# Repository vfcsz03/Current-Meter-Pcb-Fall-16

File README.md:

# Current-Meter-Pcb-Fall-16
Pcb-Design Fall 2016

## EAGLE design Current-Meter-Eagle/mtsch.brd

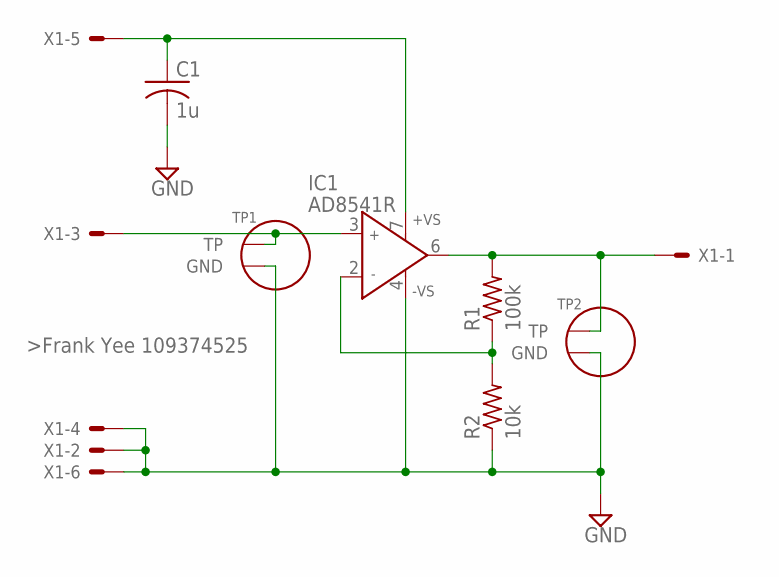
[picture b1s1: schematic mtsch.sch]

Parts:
C1: 1u; C3216
IC1: AD8541R; SO8
R1: 100k; M2012
R2: 10k; M2012
TP1, TP2: TESTPOINT; TPXPACK
X1: 22-23-2061

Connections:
GND: C1.2, IC1.4 (-VS), R2.1, TP1.GND, TP2.GND, X1.2, X1.4, X1.6
unnamed: C1.1, IC1.7 (+VS), X1.5
unnamed: IC1.3 (IN+), TP1.TP, X1.3
unnamed: IC1.6 (OUT), R1.2, TP2.TP, X1.1
unnamed: IC1.2 (IN-), R1.1, R2.2

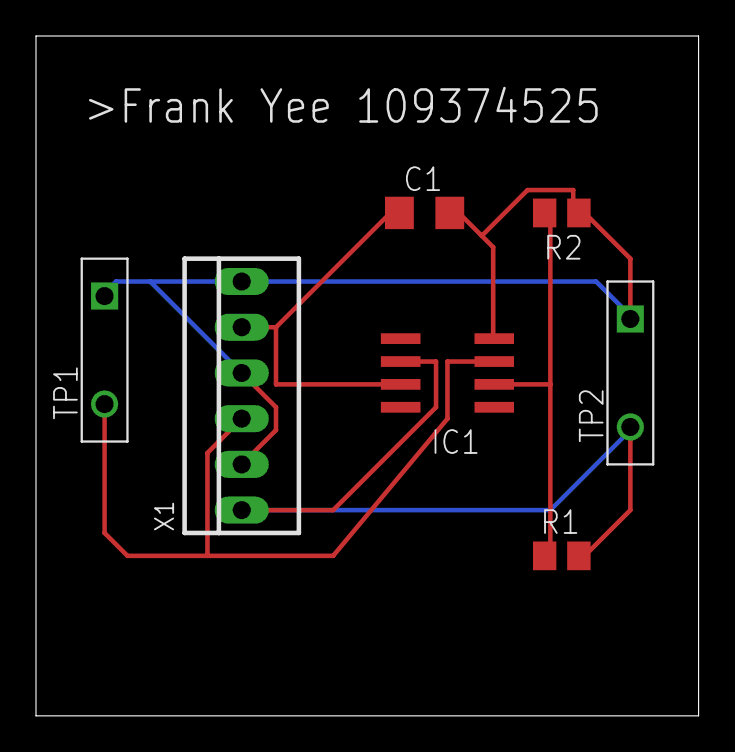
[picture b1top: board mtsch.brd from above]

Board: 2 copper layers, 36.8 x 37.8 mm, 7 parts (0 on the bottom side), 5 nets.

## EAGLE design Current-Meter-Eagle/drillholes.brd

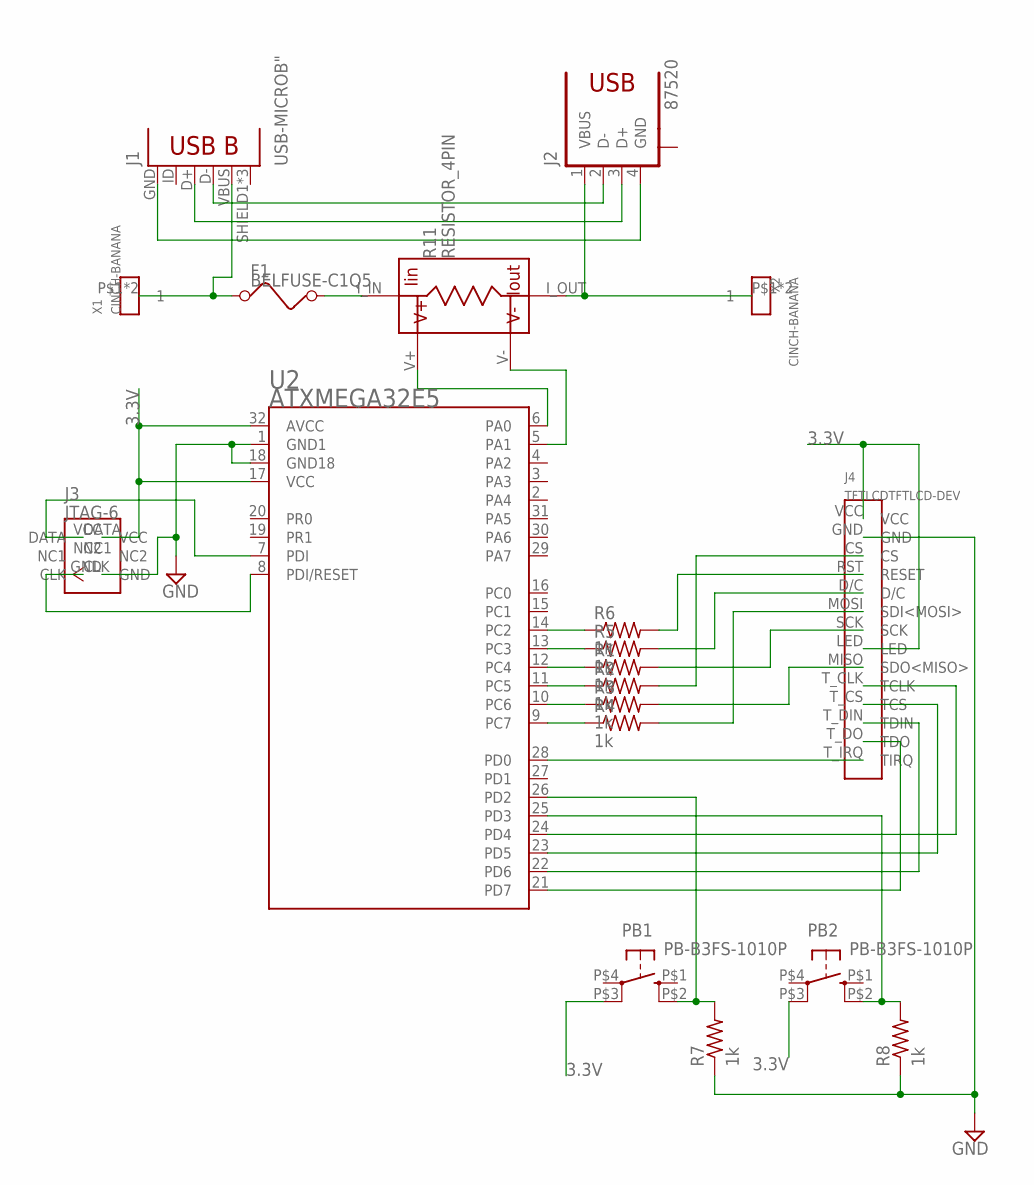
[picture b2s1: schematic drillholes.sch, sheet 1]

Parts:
ATXMEGA32E5: U2; TQFP32-08
F1: BELFUSE-C1Q5
J1: USB-MICROB"; USB-B-MICRO-SMD_V03
J2: 87520
J3: JTAG-6; JTAG6
J4: TFTLCDTFTLCD-DEV; TFTLCD
PB1, PB2: PB-B3FS-1010P
R1, R2, R3, R4, R5, R6, R7, R8: 1k; RC1206
R11: RESISTOR_4PIN
X1, X2: CINCH-BANANA

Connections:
3.3V: ATXMEGA32E5.17 (VCC), ATXMEGA32E5.32 (AVCC), J3.VCC, J4.LED, J4.VCC, PB1.P$3 (SW3), PB2.P$3 (SW3); also elsewhere on the board
GND: ATXMEGA32E5.1 (GND1), ATXMEGA32E5.18 (GND18), J3.GND, J4.GND, R7.P$1 (1), R8.P$1 (1); also elsewhere on the board
unnamed: ATXMEGA32E5.7 (PDI), J3.DATA
unnamed: ATXMEGA32E5.8 (PDI/RESET), J3.CLK
unnamed: ATXMEGA32E5.9 (PC7), R4.P$1 (1)
unnamed: ATXMEGA32E5.10 (PC6), R3.P$1 (1)
unnamed: ATXMEGA32E5.11 (PC5), R2.P$1 (1)
unnamed: ATXMEGA32E5.12 (PC4), R1.P$1 (1)
unnamed: J4.MOSI (SDI<MOSI>), R4.P$2 (2)
unnamed: J4.MISO (SDO<MISO>), R3.P$2 (2)
unnamed: J4.SCK, R1.P$2 (2)
unnamed: J4.CS, R2.P$2 (2)
unnamed: ATXMEGA32E5.14 (PC2), R6.P$1 (1)
unnamed: J4.RST (RESET), R6.P$2 (2)
unnamed: ATXMEGA32E5.13 (PC3), R5.P$1 (1)
unnamed: J4.D/C, R5.P$2 (2)
unnamed: ATXMEGA32E5.28 (PD0), J4.T_IRQ (TIRQ)
unnamed: ATXMEGA32E5.21 (PD7), J4.T_DO (TDO)
unnamed: ATXMEGA32E5.22 (PD6), J4.T_DIN (TDIN)
unnamed: ATXMEGA32E5.23 (PD5), J4.T_CS (TCS)
unnamed: ATXMEGA32E5.24 (PD4), J4.T_CLK (TCLK)
unnamed: ATXMEGA32E5.26 (PD2), PB1.P$2 (SW2), R7.P$2 (2)
unnamed: ATXMEGA32E5.25 (PD3), PB2.P$2 (SW2), R8.P$2 (2)
unnamed: ATXMEGA32E5.6 (PA0), R11.V+
unnamed: ATXMEGA32E5.5 (PA1), R11.V-
unnamed: F1.P$1 (1), J1.VBUS, X1.P$1, X1.P$2
unnamed: F1.P$2 (2), R11.I_IN
unnamed: J1.GND, J2.4 (GND)
unnamed: J1.D+, J2.3 (D+)
unnamed: J1.D-, J2.2 (D-)
unnamed: J2.1 (VBUS), R11.I_OUT, X2.P$1, X2.P$2

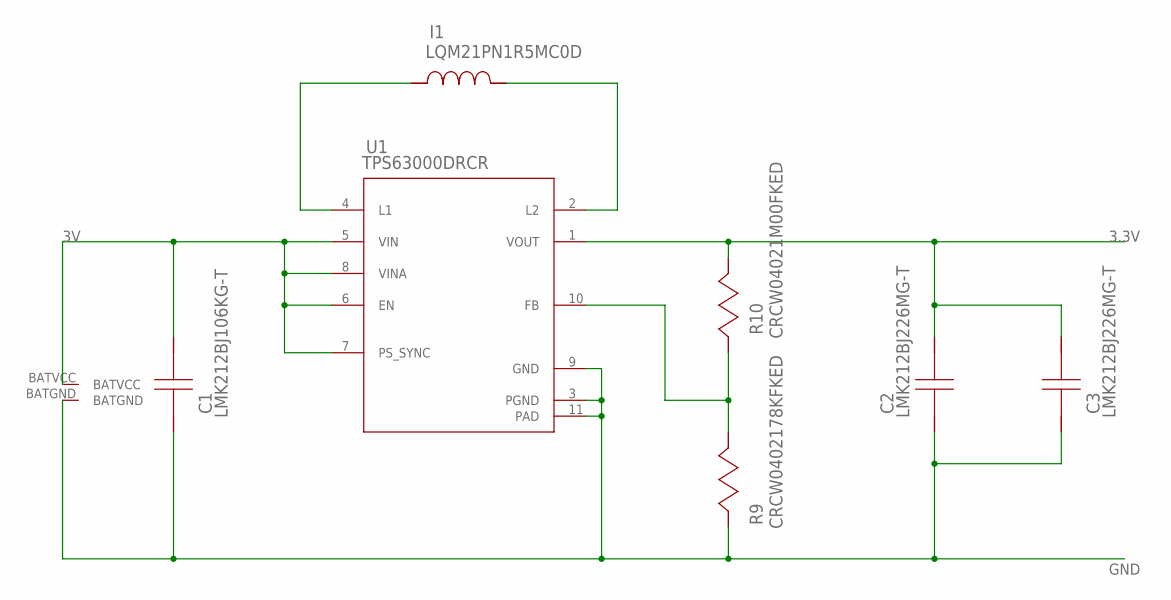
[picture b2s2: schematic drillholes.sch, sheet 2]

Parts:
C1: LMK212BJ106KG-T; 0805
C2, C3: LMK212BJ226MG-T; 0805
I1: LQM21PN1R5MC0D; 0805
R9: CRCW0402178KFKED; 0402
R10: CRCW04021M00FKED; 0402
U1: TPS63000DRCR; DRC0010J
U$12: BATTERYHOLDER

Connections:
3.3V: C2.1, C3.1, R10.1, U1.1 (VOUT); also elsewhere on the board
3V: C1.1, U1.5 (VIN), U1.6 (EN), U1.7 (PS_SYNC), U1.8 (VINA), U$12.BATVCC
GND: C1.2, C2.2, C3.2, R9.2, U1.3 (PGND), U1.9 (GND), U1.11 (PAD), U$12.BATGND; also elsewhere on the board
unnamed: I1.1, U1.4 (L1)
unnamed: I1.2, U1.2 (L2)
unnamed: R9.1, R10.2, U1.10 (FB)

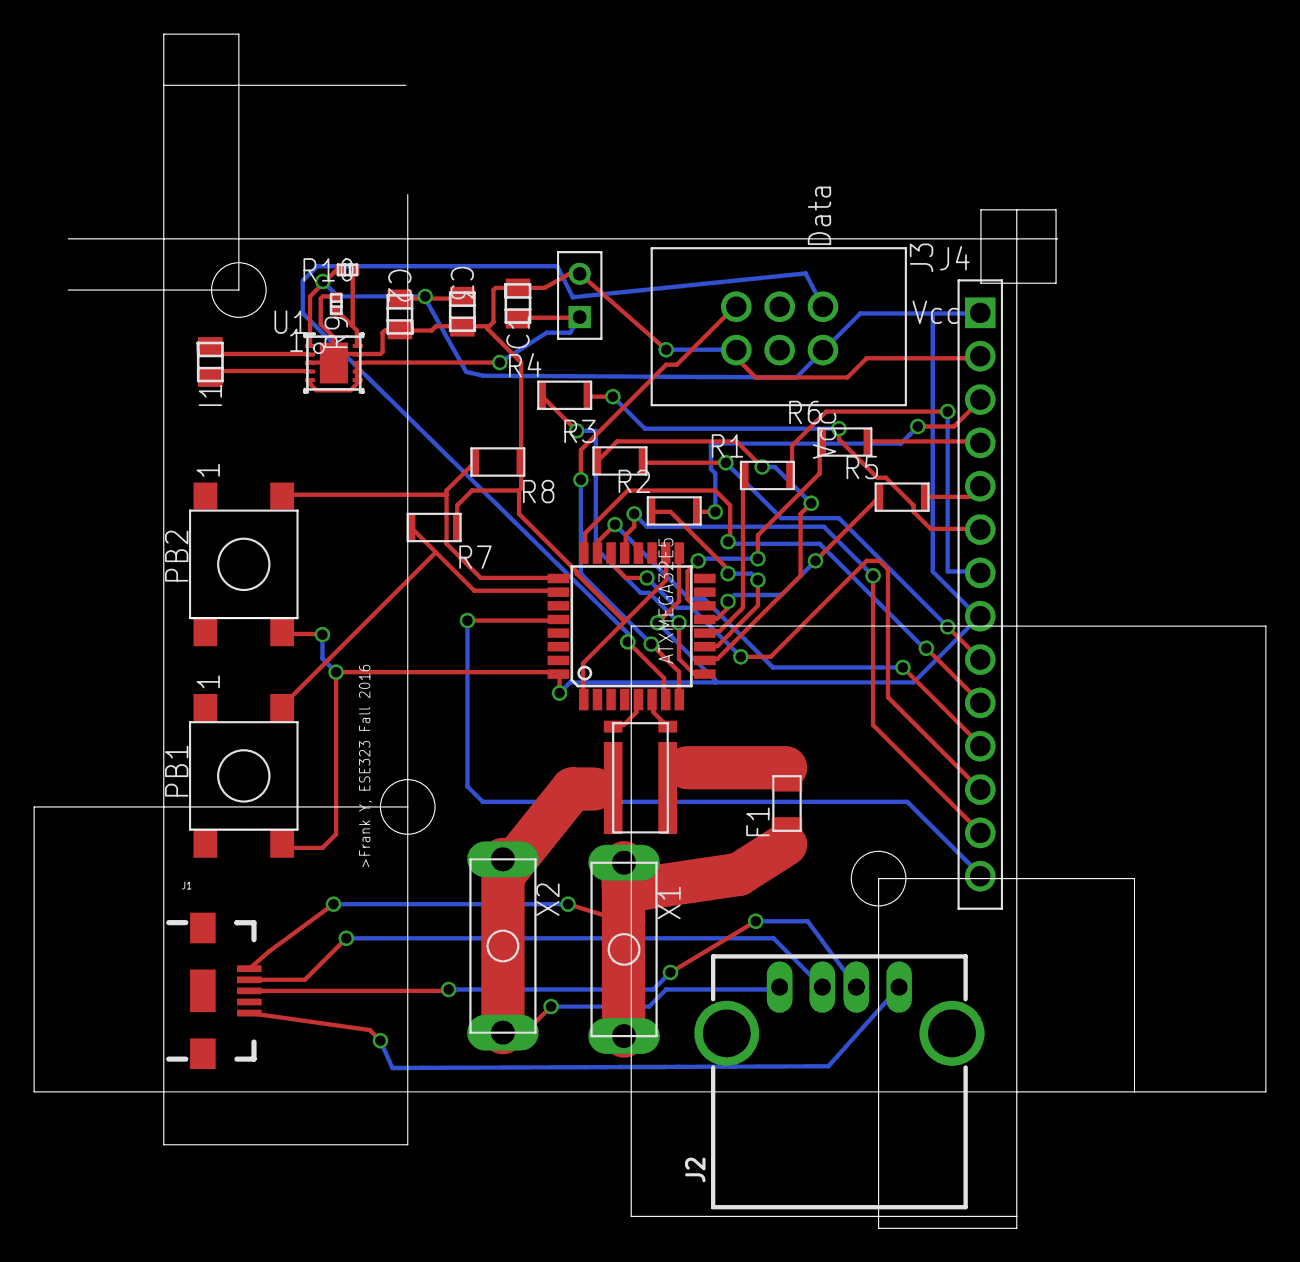
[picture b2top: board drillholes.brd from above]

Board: 2 copper layers, 72.1 x 69.9 mm, 27 parts (0 on the bottom side), 35 nets.

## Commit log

2016-10-18 :neckbeard: Added .gitattributes & .gitignore files
2016-10-18 first entry
    10/18/2016
    -sketch
2016-10-18 Create gh-pages branch via GitHub
2016-10-23 Rename ese323.lbr to Eagle-Libraries/ese323.lbr
2016-10-24 Rename README.md to READMEv1.md
2016-10-24 Rename READMEv1.md to README.md
